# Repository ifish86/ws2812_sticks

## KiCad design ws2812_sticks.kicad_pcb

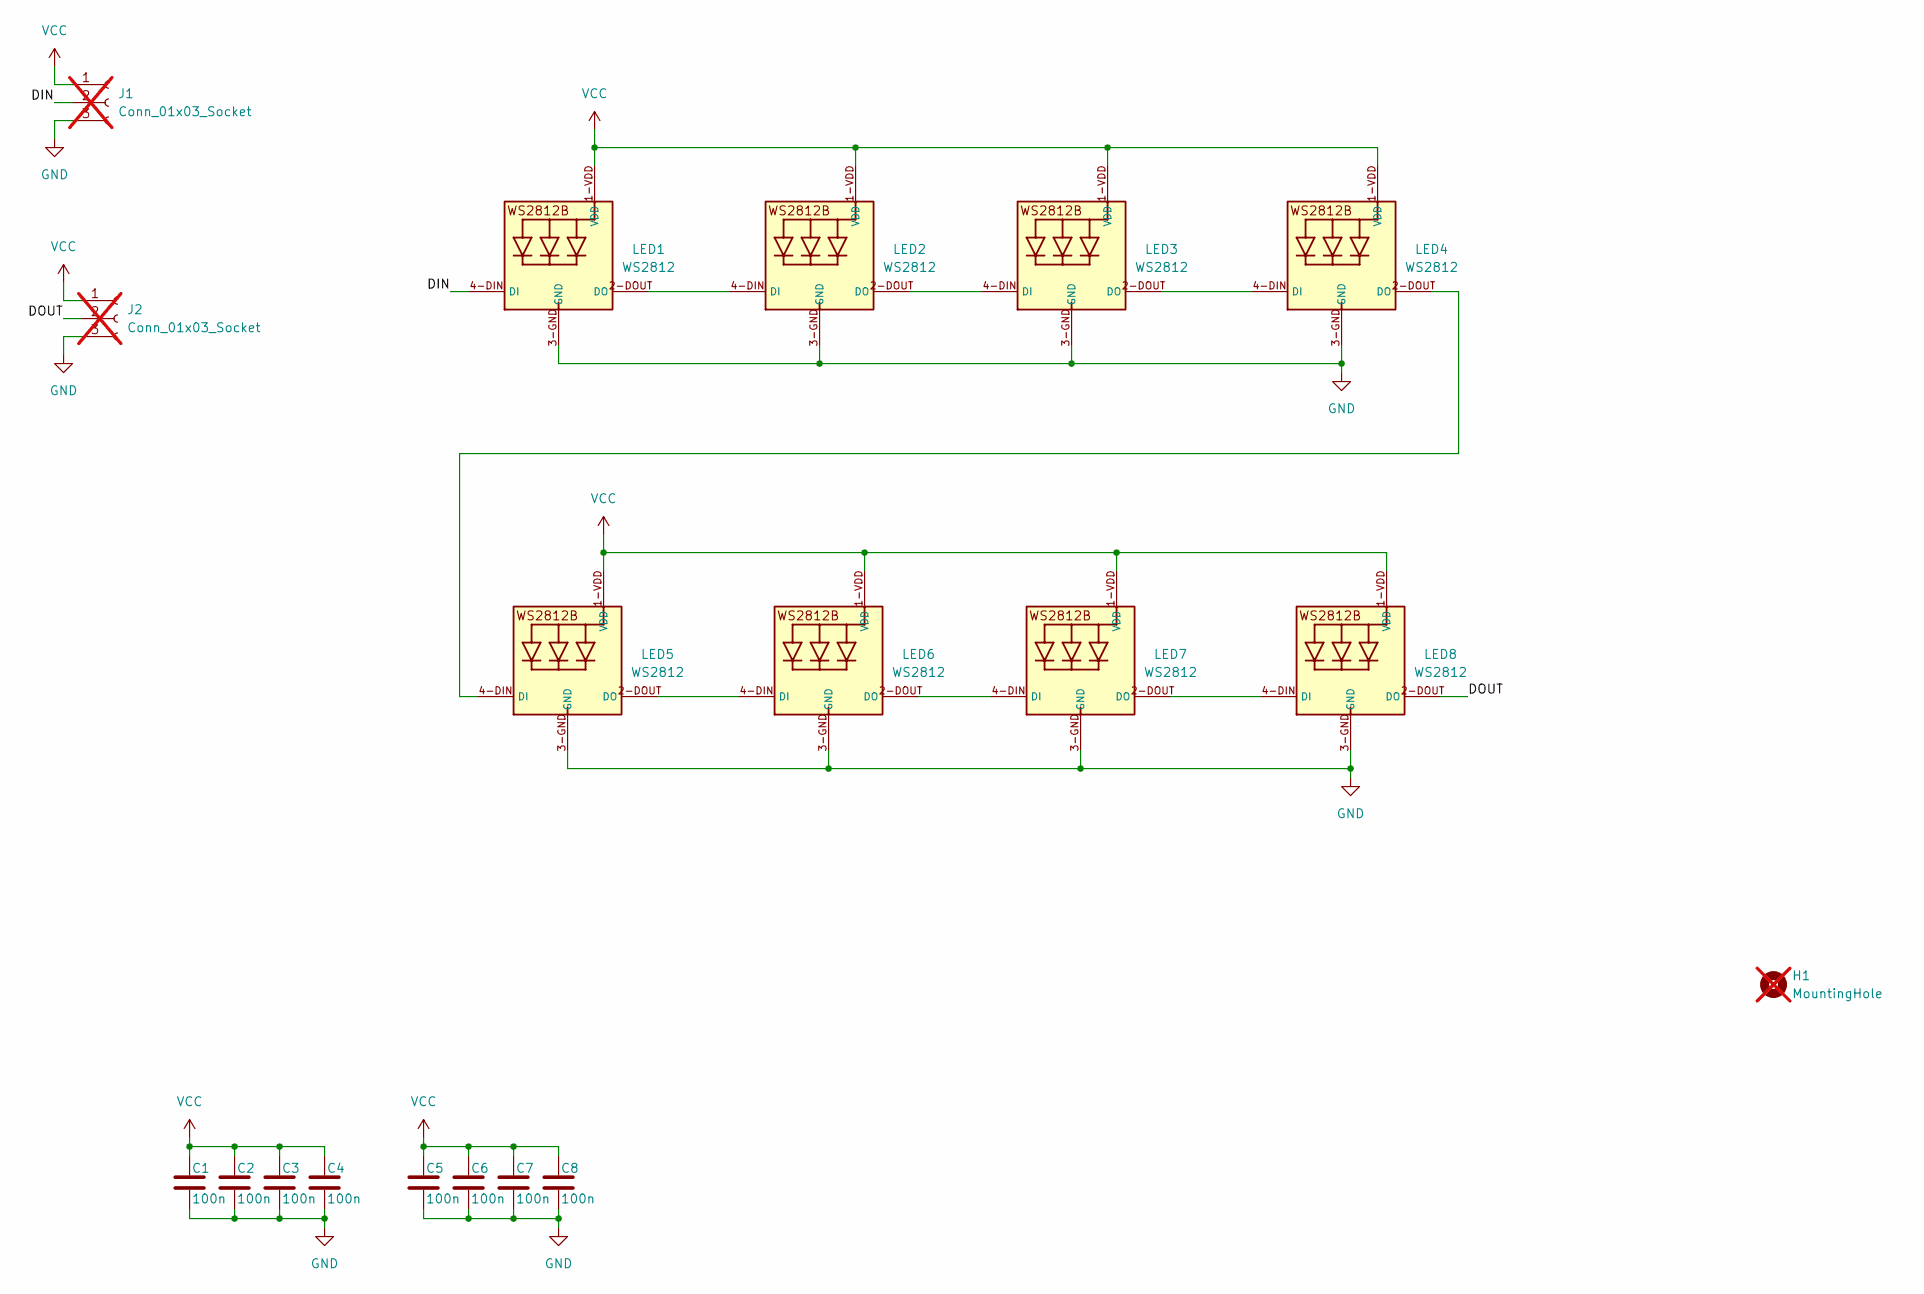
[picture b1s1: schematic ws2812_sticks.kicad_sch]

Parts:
C1, C2, C3, C4, C6, C7, C8: 100n; C_0603_1608Metric; LCSC Part # C14663
C5: 100n; C_0402_1005Metric
H1: MountingHole; MountingHole_2.2mm_M2_DIN965_Pad; not fitted
J1, J2: Conn_01x03_Socket; PinHeader_1x03_P2.54mm_Vertical; not fitted
LED1, LED2, LED3, LED4, LED5, LED6, LED7, LED8: WS2812; WS2812B_5050; LCSC Part # C2843785

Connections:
/DIN: J1.2, LED1.4-DIN (DI)
/DOUT: J2.2, LED8.2-DOUT (DO)
GND: C1.2, C2.2, C3.2, C4.2, C5.2, C6.2, C7.2, C8.2, J1.3, J2.3, LED1.3-GND (GND), LED2.3-GND (GND), LED3.3-GND (GND), LED4.3-GND (GND), LED5.3-GND (GND), LED6.3-GND (GND), LED7.3-GND (GND), LED8.3-GND (GND)
unnamed: LED1.2-DOUT (DO), LED2.4-DIN (DI)
unnamed: LED2.2-DOUT (DO), LED3.4-DIN (DI)
unnamed: LED3.2-DOUT (DO), LED4.4-DIN (DI)
unnamed: LED4.2-DOUT (DO), LED5.4-DIN (DI)
unnamed: LED5.2-DOUT (DO), LED6.4-DIN (DI)
unnamed: LED6.2-DOUT (DO), LED7.4-DIN (DI)
unnamed: LED7.2-DOUT (DO), LED8.4-DIN (DI)
VCC: C1.1, C2.1, C3.1, C4.1, C5.1, C6.1, C7.1, C8.1, J1.1, J2.1, LED1.1-VDD (VDD), LED2.1-VDD (VDD), LED3.1-VDD (VDD), LED4.1-VDD (VDD), LED5.1-VDD (VDD), LED6.1-VDD (VDD), LED7.1-VDD (VDD), LED8.1-VDD (VDD)

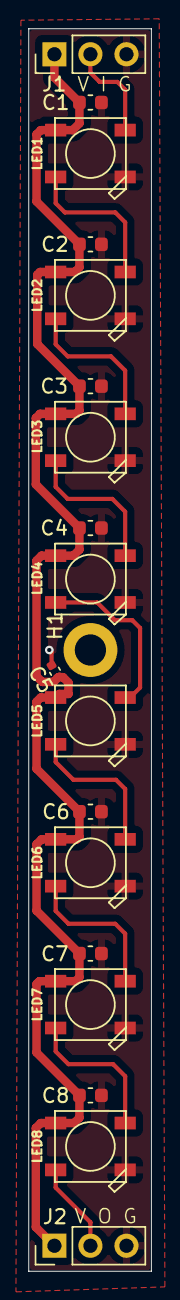
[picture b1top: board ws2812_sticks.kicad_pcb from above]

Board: 2 copper layers, 8.7 x 87.6 mm, 19 parts (0 on the bottom side), 11 nets.

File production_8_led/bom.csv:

Designator,Footprint,Quantity,Value,LCSC Part #
"C1, C2, C3, C4, C6, C7, C8",0603,7,100n,C14663
C5,0402,1,100n,
"LED1, LED2, LED3, LED4, LED5, LED6, LED7, LED8",WS2812B_5050,8,WS2812,C2843785

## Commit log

2025-09-05 initial commit, 4 led version commplete
2025-09-07 created 8 led version
